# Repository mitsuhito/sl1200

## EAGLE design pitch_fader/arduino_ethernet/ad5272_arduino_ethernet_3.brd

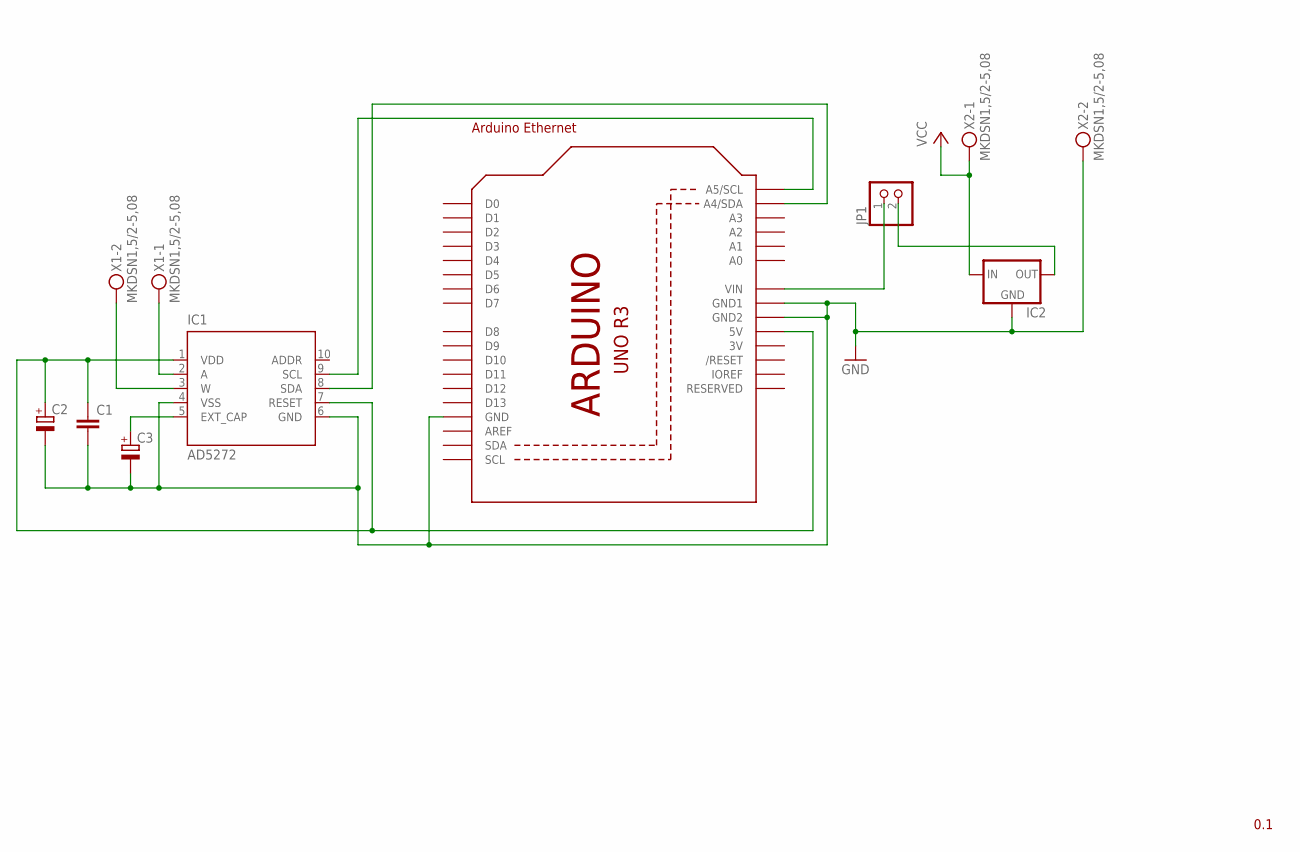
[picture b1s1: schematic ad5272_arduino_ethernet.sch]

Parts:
C1: C-EU050-024X044; C050-024X044
C2, C3: CPOL-EUE2.5-7; E2,5-7
IC1: AD5272; MSOP10
IC2: 78XXL
JP1: PINHD-1X2; 1X02
U1: ARDUINOR3-DIMENSION; ARDUINOR3
X1, X2: MKDSN1,5/2-5,08

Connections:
3V: U1.3V
GND: C1.2, C2.-, C3.-, IC1.4 (VSS), IC1.6 (GND), IC2.GND, U1.GND, U1.GND1, U1.GND2, X2.2
unnamed: IC1.9 (SCL), U1.A5 (A5/SCL)
unnamed: IC1.8 (SDA), U1.A4 (A4/SDA)
unnamed: IC2.OUT, JP1.2
unnamed: C3.+, IC1.5 (EXT_CAP)
unnamed: C1.1, C2.+, IC1.1 (VDD), IC1.7 (RESET), U1.5V
unnamed: IC1.3 (W), X1.2
unnamed: IC1.2 (A), X1.1
unnamed: JP1.1, U1.VIN
VCC: IC2.IN, X2.1

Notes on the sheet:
0.1
Arduino Ethernet

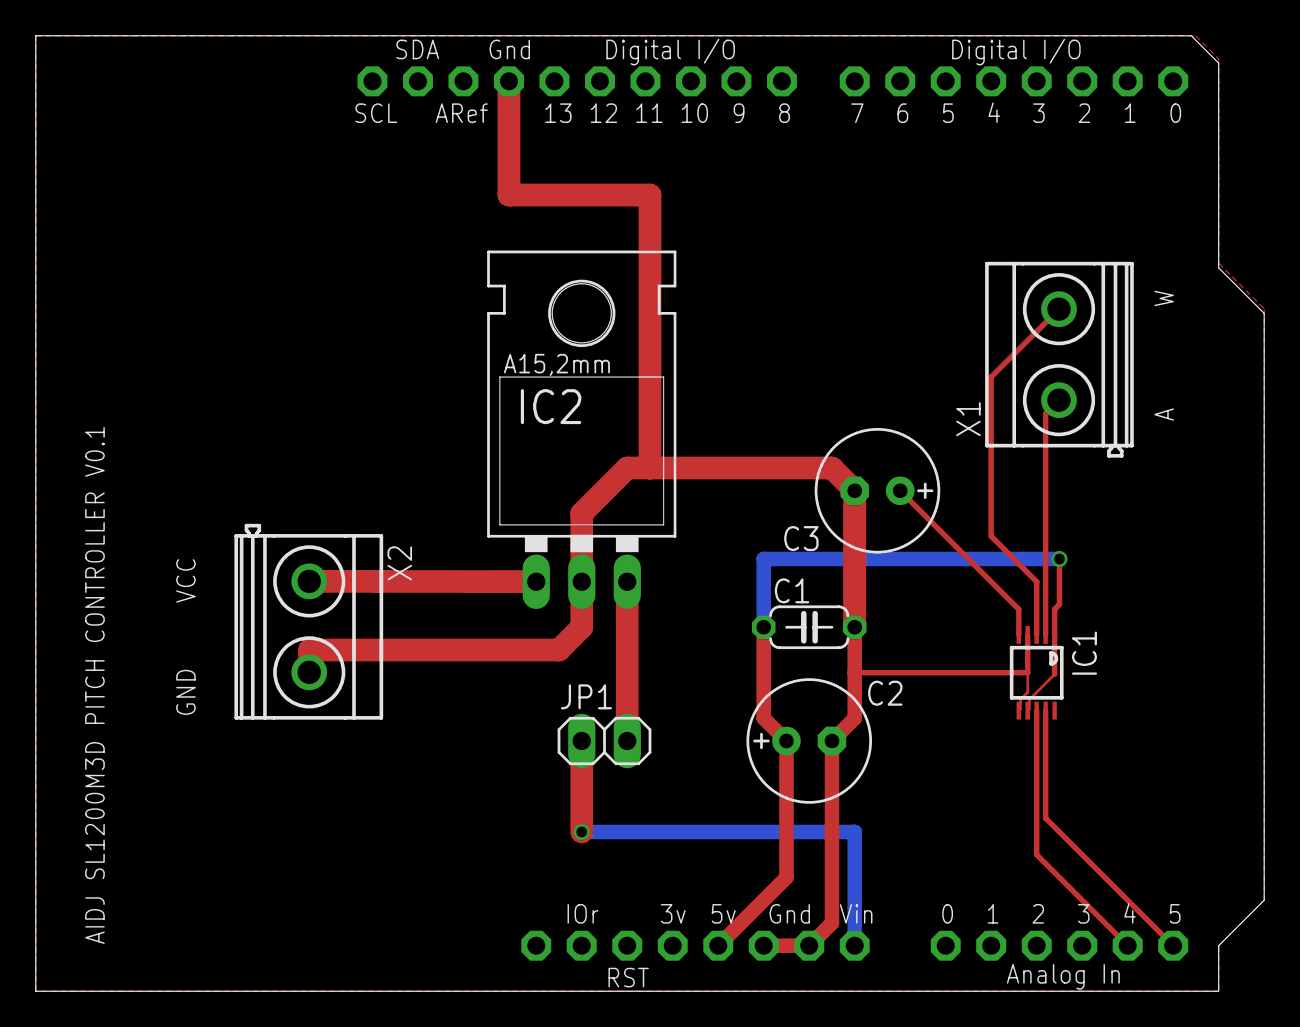
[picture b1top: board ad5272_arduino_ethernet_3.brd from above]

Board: 2 copper layers, 68.6 x 53.3 mm, 9 parts (0 on the bottom side), 10 nets.

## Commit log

2017-10-31 add arduino sketch
2017-10-31 add eagle files
2017-10-31 move eagle files
